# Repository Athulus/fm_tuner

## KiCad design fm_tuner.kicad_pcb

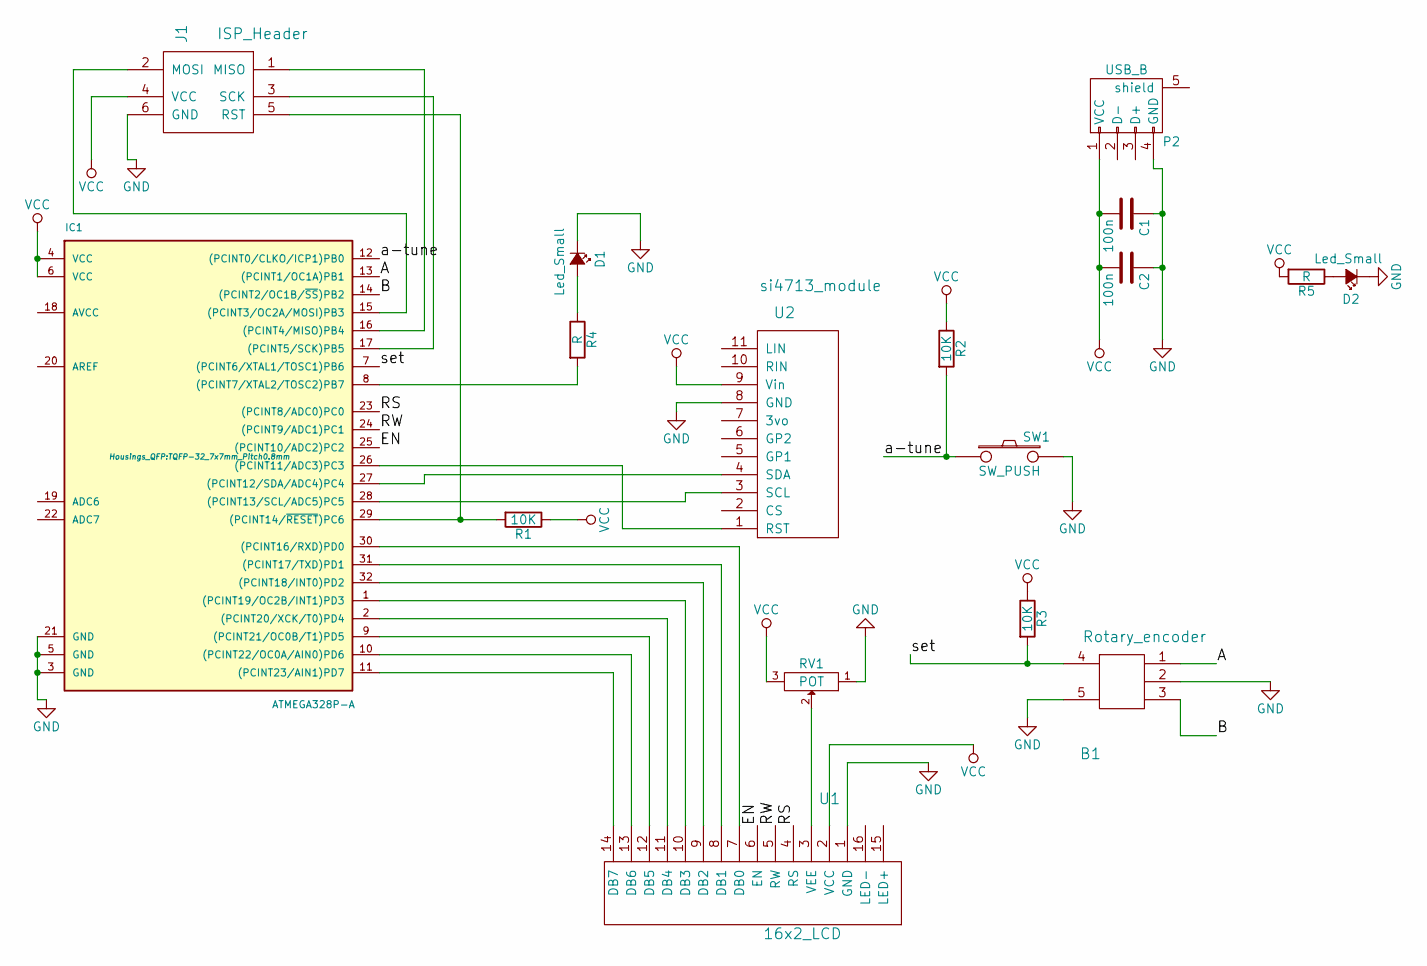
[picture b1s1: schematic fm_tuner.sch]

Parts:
B1: Rotary_encoder; rotary_encoder
C1, C2: 100n; C_0805_HandSoldering
D1, D2: Led_Small; SMA_Standard
IC1: ATMEGA328P-A; TQFP-32_7x7mm_Pitch0.8mm
J1: ISP_Header; Pin_Header_Straight_2x03
P2: USB_B; USB_Micro-B
R1, R2, R3: 10K; R_0805_HandSoldering
R4, R5: R; R_0805_HandSoldering
RV1: POT; POT_SMD
SW1: SW_PUSH; SW_SPST_EVQP0
U1: 16x2_LCD; 16x2_LCD_noscreen
U2: si4713_module; Pin_Header_Straight_1x11

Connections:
/A: B1.1, IC1.13 ((PCINT1/OC1A)PB1)
/B: B1.3, IC1.14 ((PCINT2/OC1B/~SS~)PB2)
/EN: IC1.25 ((PCINT10/ADC2)PC2), U1.6 (EN)
/RS: IC1.23 ((PCINT8/ADC0)PC0), U1.4 (RS)
/RW: IC1.24 ((PCINT9/ADC1)PC1), U1.5 (RW)
/a-tune: IC1.12 ((PCINT0/CLKO/ICP1)PB0), R2.2, SW1.1
/set: B1.4, IC1.7 ((PCINT6/XTAL1/TOSC1)PB6), R3.2
GND: B1.2, B1.5, C1.1, C2.1, D1.1 (K), D2.1 (K), IC1.3 (GND), IC1.5 (GND), IC1.21 (GND), J1.6 (GND), P2.4 (GND), RV1.1, SW1.2, U1.1 (GND), U2.8 (GND)
unnamed: D1.2 (A), R4.1
unnamed: D2.2 (A), R5.1
unnamed: IC1.1 ((PCINT19/OC2B/INT1)PD3), U1.10 (DB3)
unnamed: IC1.2 ((PCINT20/XCK/T0)PD4), U1.11 (DB4)
unnamed: IC1.8 ((PCINT7/XTAL2/TOSC2)PB7), R4.2
unnamed: IC1.9 ((PCINT21/OC0B/T1)PD5), U1.12 (DB5)
unnamed: IC1.10 ((PCINT22/OC0A/AIN0)PD6), U1.13 (DB6)
unnamed: IC1.11 ((PCINT23/AIN1)PD7), U1.14 (DB7)
unnamed: IC1.15 ((PCINT3/OC2A/MOSI)PB3), J1.2 (MOSI)
unnamed: IC1.16 ((PCINT4/MISO)PB4), J1.1 (MISO)
unnamed: IC1.17 ((PCINT5/SCK)PB5), J1.3 (SCK)
unnamed: IC1.26 ((PCINT11/ADC3)PC3), U2.1 (RST)
unnamed: IC1.27 ((PCINT12/SDA/ADC4)PC4), U2.4 (SDA)
unnamed: IC1.28 ((PCINT13/SCL/ADC5)PC5), U2.3 (SCL)
unnamed: IC1.29 ((PCINT14/~RESET~)PC6), J1.5 (RST), R1.2
unnamed: IC1.30 ((PCINT16/RXD)PD0), U1.7 (DB0)
unnamed: IC1.31 ((PCINT17/TXD)PD1), U1.8 (DB1)
unnamed: IC1.32 ((PCINT18/INT0)PD2), U1.9 (DB2)
unnamed: RV1.2, U1.3 (VEE)
VCC: C1.2, C2.2, IC1.4 (VCC), IC1.6 (VCC), J1.4 (VCC), P2.1 (VCC), R1.1, R2.1, R3.1, R5.2, RV1.3, U1.2 (VCC), U2.9 (Vin)

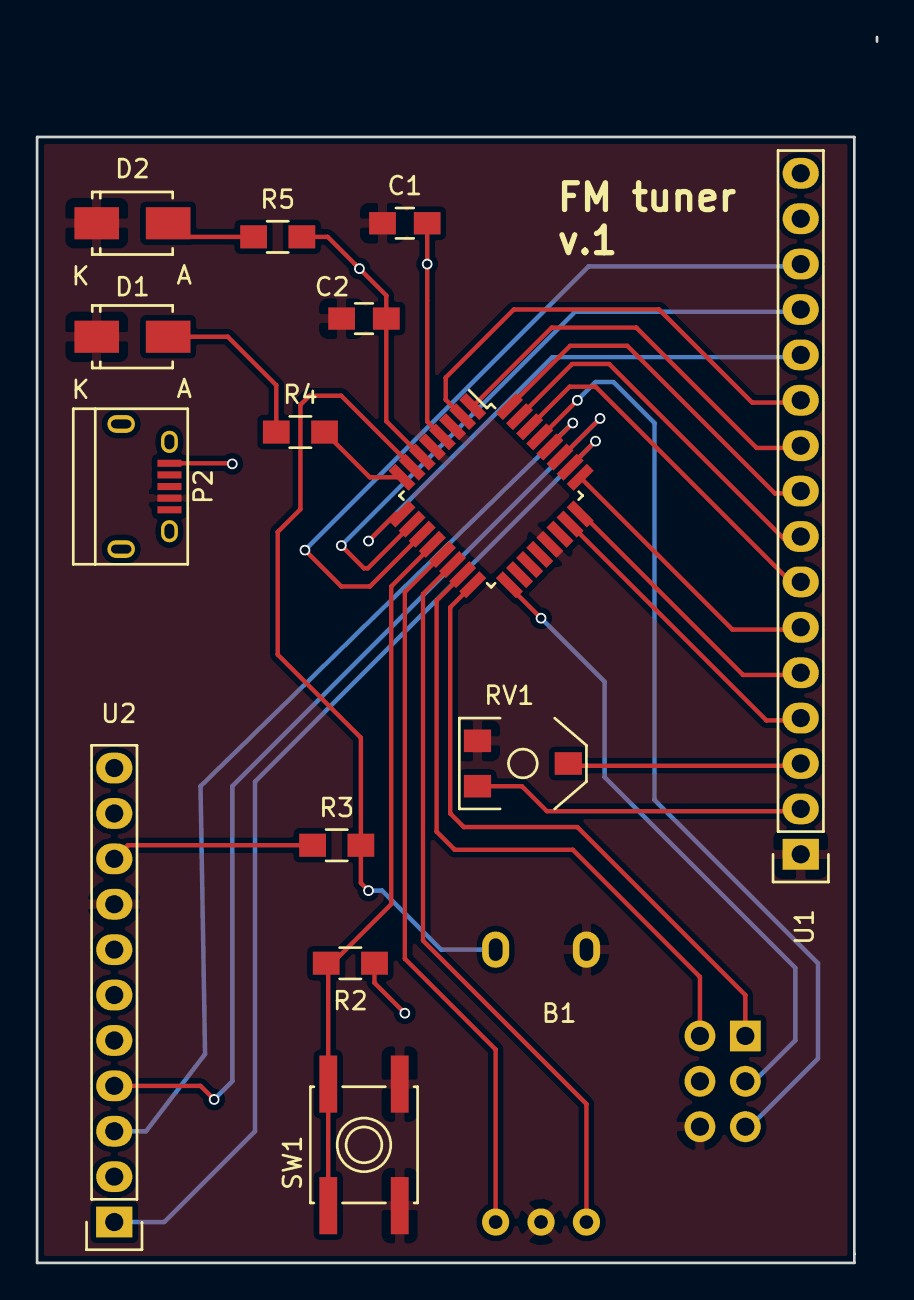
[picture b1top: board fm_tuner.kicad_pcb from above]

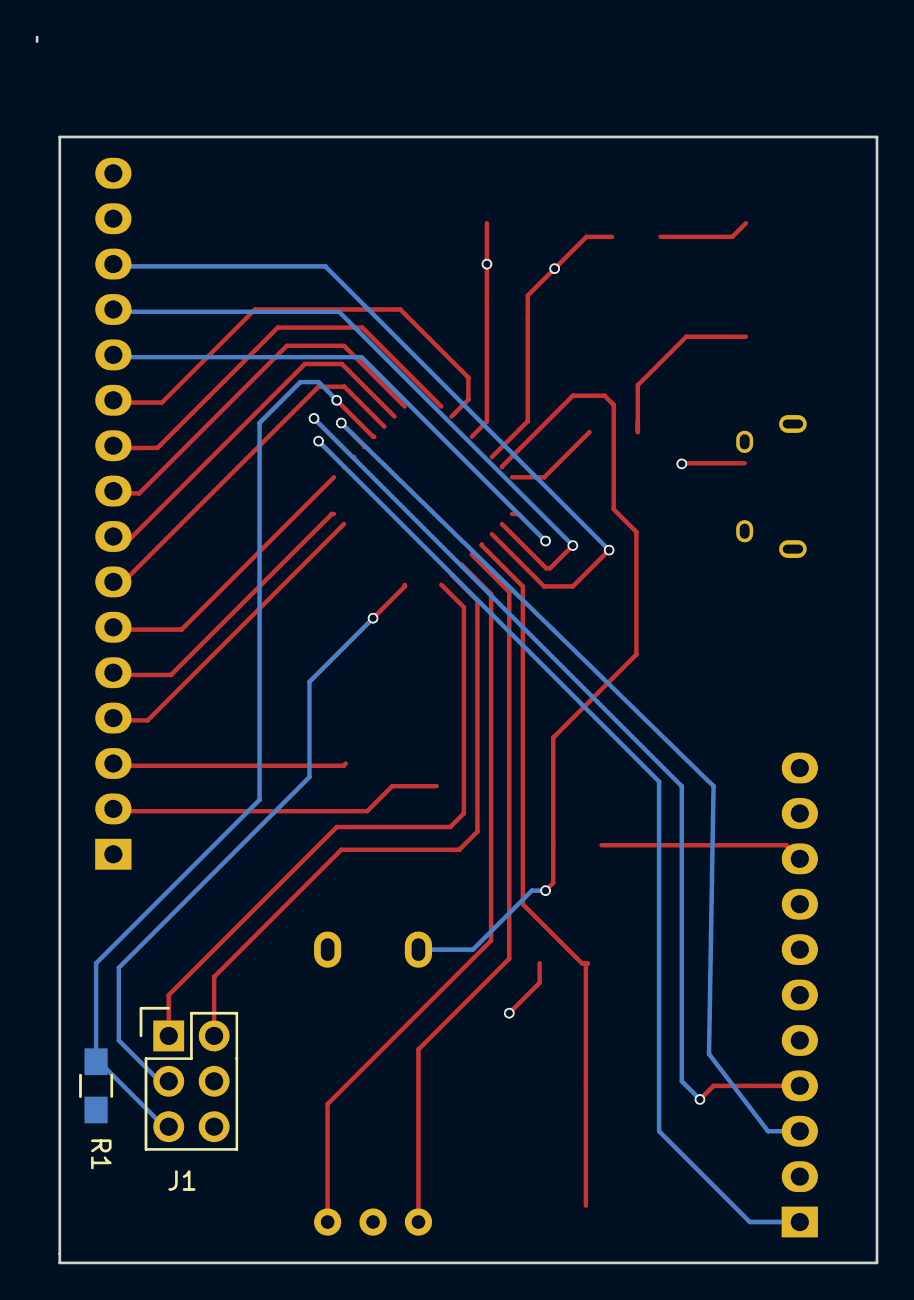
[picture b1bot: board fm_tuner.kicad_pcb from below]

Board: 2 copper layers, 47.0 x 68.6 mm, 17 parts (2 on the bottom side), 28 nets.

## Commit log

2016-02-22 first commit. schematic and netlist already done
2016-02-22 added first pass of routes to the board
2016-02-24 finished routing? added text description to board. created fabrication outputs(gerber and drill files)
2016-02-28 added a new footprint for LCD with no silkscreen outline of the screen replaced LCD footprint on board wiht new one changed pour clearance
2016-02-28 remade gerbers
